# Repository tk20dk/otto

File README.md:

# otto
433MHz high power LoRa USB gateway

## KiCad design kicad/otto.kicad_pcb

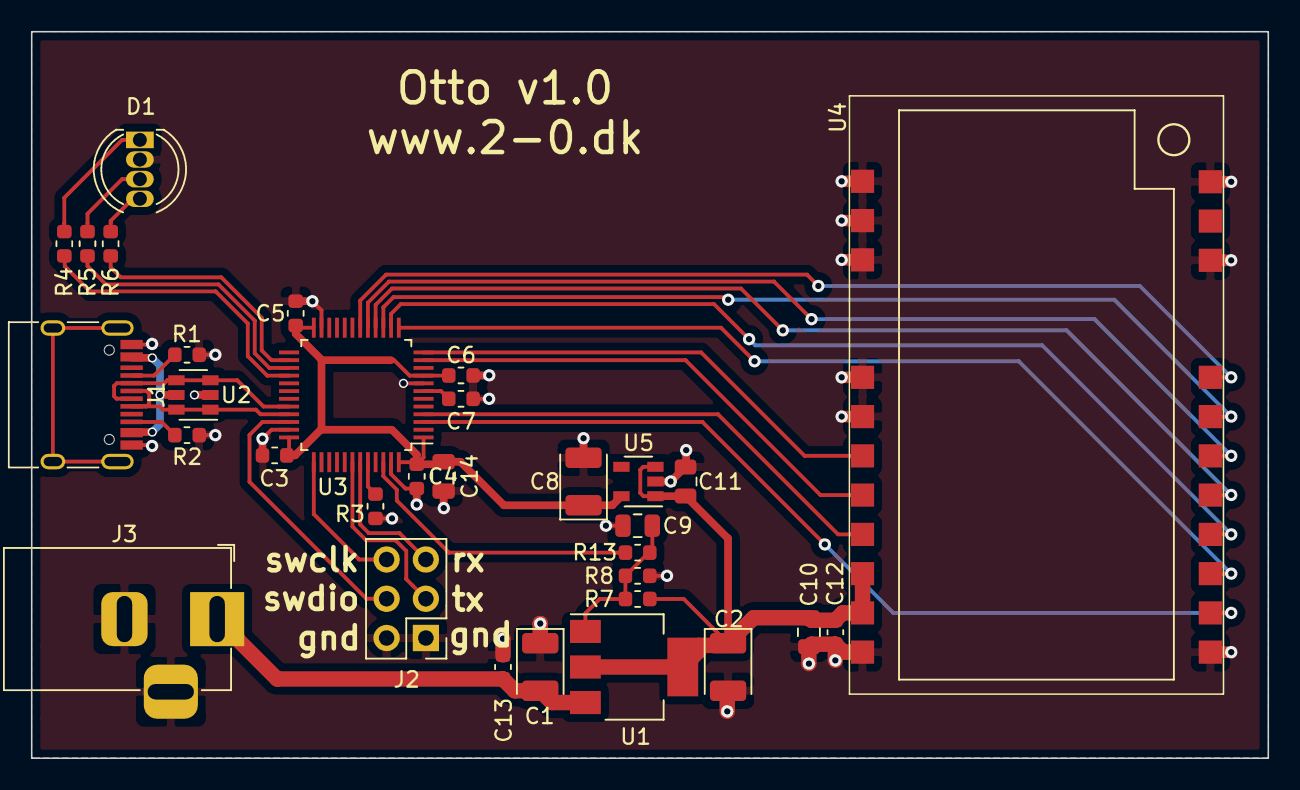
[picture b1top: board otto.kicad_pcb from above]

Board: 2 copper layers, 80.0 x 47.0 mm, 32 parts (0 on the bottom side), 33 nets.

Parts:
C1, C2, C8: 10u; CP_EIA-3528-12_Kemet-T
C3, C4, C5, C6, C7, C12, C13: 100n; C_0603_1608Metric
C9, C10: 10u; C_0805_2012Metric
C11: 1u; C_0805_2012Metric
C14: 4,7u; C_0805_2012Metric
D1: LED_RCGB; LED_D5.0mm-4
J1: USB-C; USB_C_Receptacle_HRO_TYPE-C-31-M-12
J2: Debug; PinHeader_2x03_P2.54mm_Vertical
J3: 9V; BarrelJack_Horizontal
R1, R2: 5k1; R_0603_1608Metric
R3: 100k; R_0603_1608Metric
R4, R5, R6: 470; R_0603_1608Metric
R7, R8, R13: R; R_0603_1608Metric
U1: AMS1117; SOT-223-3_TabPin2
U2: SRV05-4; SOT-23-6
U3: STM32F072C8Tx; LQFP-48_7x7mm_P0.5mm
U4: E22-400M30S
U5: LP5907MFX-3.3; SOT-23-5

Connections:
+3V3: C3.1, C4.1, C5.1, C6.1, C8.1, C14.1, U3.1, U3.9, U3.24, U3.36, U3.48, U5.5
+5V: C2.1, C10.1, C11.1, C12.1, R7.1, U1.2, U4.9, U4.10, U5.1, U5.3
GND: C1.1, C2.2, C3.2, C4.2, C5.2, C6.2, C7.2, C8.2, C9.2, C10.2, C11.2, C12.2, C13.2, C14.2, D1.2, J1.A1, J1.A12, J1.B1, J1.B12, J2.1, J2.2, J3.2, J3.3, R1.1, R2.1, R3.2, R8.2, U2.2, U3.8, U3.23, U3.35, U3.47, U4.1, U4.2, U4.3, U4.4, U4.5, U4.11, U4.12, U4.20, U4.22, U5.2
unnamed: C1.2, C13.1, J3.1, U1.3
unnamed: C9.1, R7.2, R8.1, R13.1, U1.1
unnamed: D1.1, R4.2
unnamed: D1.3, R5.2
unnamed: D1.4, R6.2
unnamed: J1.A5, R1.2
unnamed: J1.B5, R2.2
boot0: R3.1, U3.44
dac_adj: R13.2, U3.46
led1_blue: R6.1, U3.26
led1_green: R5.1, U3.27
led1_red: R4.1, U3.28
nrst: C7.1, U3.7
radio_busy: U3.13, U4.14
radio_dio1: U3.3, U4.13
radio_dio2: U3.4, U4.8
radio_nrst: U3.14, U4.15
radio_nss: U3.18, U4.19
radio_rxen: U3.12, U4.6
radio_txen: U3.11, U4.7
spi_miso: U3.16, U4.16
spi_mosi: U3.17, U4.17
spi_sck: U3.15, U4.18
swclk: J2.6, U3.37
swdio: J2.4, U3.34
uart_rx: J2.5, U3.43
uart_tx: J2.3, U3.42
usb_dm: J1.A7, J1.B7, U2.3, U2.4, U3.32
usb_dp: J1.A6, J1.B6, U2.1, U2.6, U3.33
vusb: J1.A4, J1.A9, J1.B4, J1.B9, U2.5

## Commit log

2020-11-25 initial pcb design
